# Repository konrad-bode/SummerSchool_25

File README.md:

# HeiChips 2025 SummerSchool – FPGA Carrier Board

This repository contains the KiCad hardware design for the **HeiChips 2025 SummerSchool FPGA Carrier Board**, designed to interface with the custom tapeout FPGA chip from the [HeiChips 2025 Tapeout Repository](https://github.com/HeiChips/heichips25-tapeout).

---

## 🏗 System Overview

The carrier board interfaces with a custom HeiChips FPGA breakout module via a 70-pin high-density mezzanine connector. An onboard RP2350A microcontroller handles FPGA configuration.

---

## ⚡ Key Hardware Features

### Onboard Controller & Configuration
* **Microcontroller:** RP2350A MCU managing FPGA boot configuration (`FPGA_CONFIG_SLOT[0..3]`), reset, clocks, and SPI interface.
* **Flash Memory:** Dual W25Q32JVSS QSPI Flash ICs (one for RP2350, one for FPGA image storage).
* **Control Switches:** 74LVC1G66 analog switch for SPI bus arbitration.

### Power Management
* **Input Power:** 5V DC input via USB-C
* **System 3.3V:** TLV1117-33 LDO supplying 3.3V rail from 5V input for FPGA IO and Microcontroller
* **FPGA Core Supply (`VCORE`/`AVCORE`):** AP7361C adjustable LDO 

### Connectors & Peripherals
* **Module Interconnect:** 70-pin Amphenol BergStak Mezzanine Receptacle (`10164227-0701A1RLF`).
* **Expansion:** 4x PMOD headers (`J20`–`J23`) routing FPGA `GPIO0`–`GPIO31`.
* **Video Output:** HDMI interface (`J18`) driven by DS90LV027A LVDS differential line drivers.
* **USB Ports:** Dual USB-C connectors (`J17` for RP2350 debug/programming, `J19` directly connected to FPGA USB with ESD protection).
* **Analog & RF:** Coaxial SMA/MCX connectors for IceLab analog pins, internal analog signals, and Pudding I/O lines.
* **Ethernet:** 3-pin Ethernet header (`J8`).

---

## TODO
- [ ] HDMI differential pair length matching and impedance tuning.
- [ ] Project selection per jumper
- [ ] Connect GPIOs from FPGA to Microcontroller UART? 
- [ ] Check SMA distance

---

## 👤 Author
* **Konrad Bode**

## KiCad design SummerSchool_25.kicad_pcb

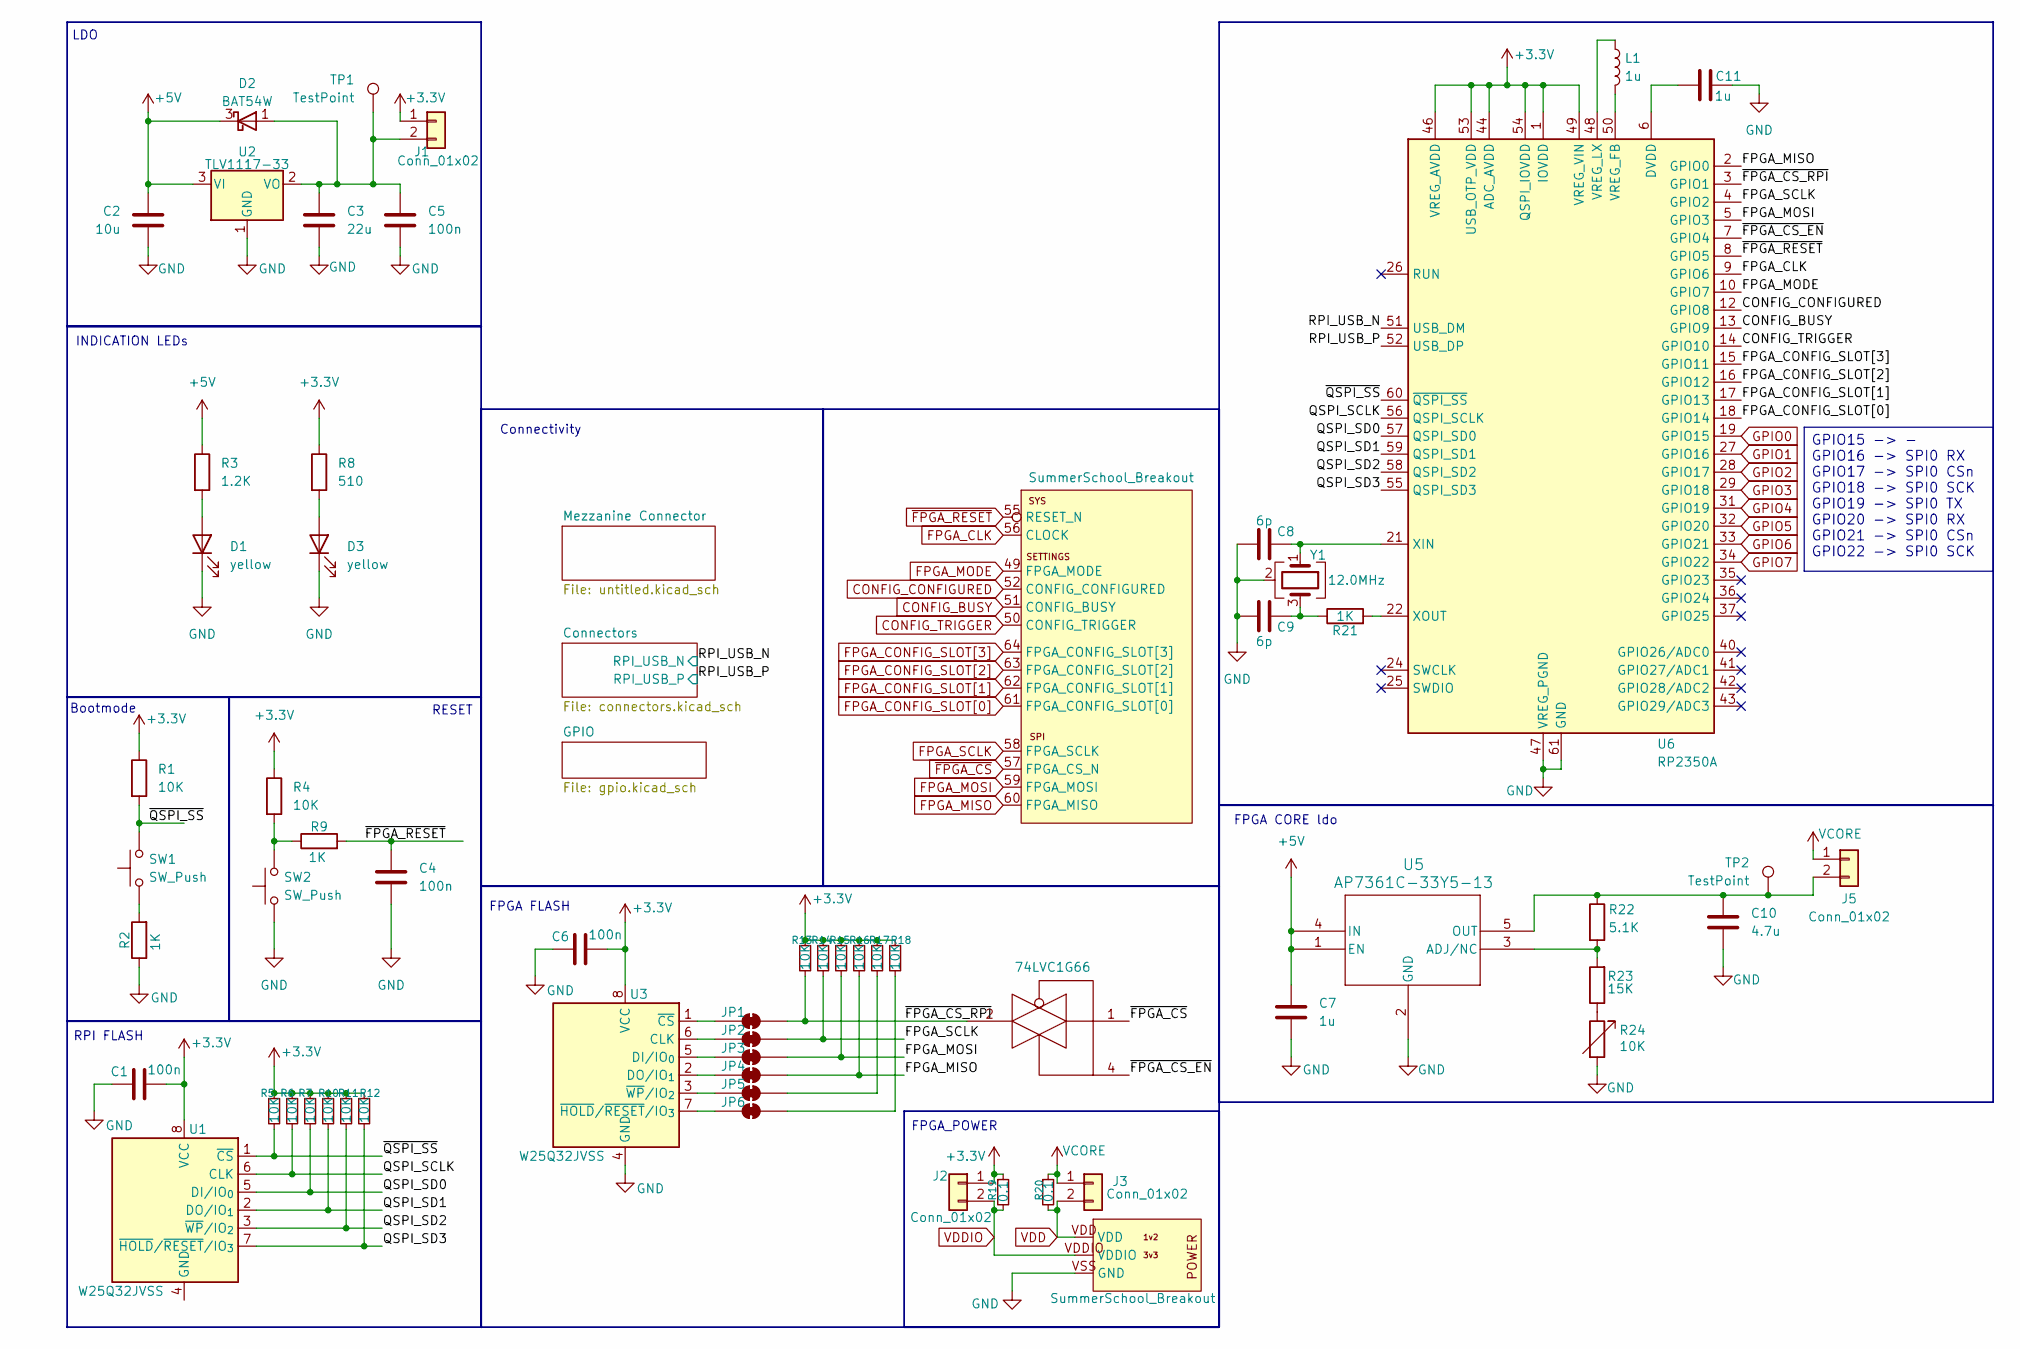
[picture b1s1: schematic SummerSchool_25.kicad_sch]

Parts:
C1, C4, C5, C6: 100n; C_0603_1608Metric
C2: 10u; C_0603_1608Metric
C3: 22u; C_0603_1608Metric
C7, C11: 1u; C_0603_1608Metric
C8, C9: 6p; C_0603_1608Metric
C10: 4.7u; C_0603_1608Metric
D1, D3: yellow; LED_0603_1608Metric
D2: BAT54W; SOT-323_SC-70
J1, J2, J3, J5: Conn_01x02; PinHeader_1x02_P2.54mm_Vertical
J4: SummerSchool_Breakout; SummerSchool_WireBond
JP1, JP2, JP3, JP4, JP5, JP6: SolderJumper_2_Bridged; SolderJumper-2_P1.3mm_Bridged2Bar_RoundedPad1.0x1.5mm
L1: 1u; L_1008_2520Metric
R1, R4, R5, R6, R7, R10, R11, R12, R13, R14, R15, R16, R17, R18: 10K; R_0402_1005Metric
R2, R9, R21: 1K; R_0402_1005Metric
R3: 1.2K; R_0402_1005Metric
R8: 510; R_0402_1005Metric
R19, R20: 0.1; R_0805_2012Metric
R22: 5.1K; R_0402_1005Metric
R23: 15K; R_0402_1005Metric
R24: 10K; R_LDR_5.2x5.2mm_P3.5mm_Horizontal
SW1, SW2: SW_Push; SW_SPST_EVQP2_MiddlePushTravel_H2.5mm
TP1, TP2: TestPoint; TestPoint_Pad_1.5x1.5mm
U1, U3: W25Q32JVSS; SOIC-8_5.3x5.3mm_P1.27mm
U2: TLV1117-33; TO-252-2
U4: 74LVC1G66; SOT-553
U5: AP7361C-33Y5-13; SOT89-5_DIO
U6: RP2350A; QFN-60-1EP_7x7mm_P0.4mm_EP3.4x3.4mm
Y1: 12.0MHz; Crystal_SMD_3225-4Pin_3.2x2.5mm

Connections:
+3.3V: C1.2, C6.2, J1.1, J2.1, R1.1, R4.1, R5.1, R6.1, R7.1, R8.1, R10.1, R11.1, R12.1, R13.1, R14.1, R15.1, R16.1, R17.1, R18.1, R19.1, U1.8 (VCC), U3.8 (VCC), U6.1 (IOVDD), U6.11 (IOVDD), U6.20 (IOVDD), U6.30 (IOVDD), U6.38 (IOVDD), U6.44 (ADC_AVDD), U6.45 (IOVDD), U6.46 (VREG_AVDD), U6.49 (VREG_VIN), U6.53 (USB_OTP_VDD), U6.54 (QSPI_IOVDD); also elsewhere on the board
+5V: C2.1, C7.1, D2.3 (K), R3.1, U2.3 (VI), U5.1 (EN), U5.4 (IN); also elsewhere on the board
/QSPI_SCLK: R6.2, U1.6 (CLK), U6.56 (QSPI_SCLK)
/QSPI_SD0: R7.2, U1.5 (DI/IO_{0}), U6.57 (QSPI_SD0)
/QSPI_SD1: R10.2, U1.2 (DO/IO_{1}), U6.59 (QSPI_SD1)
/QSPI_SD2: R11.2, U1.3 (~WP/IO_{2}), U6.58 (QSPI_SD2)
/QSPI_SD3: R12.2, U1.7 (~HOLD/~RESET/IO_{3}), U6.55 (QSPI_SD3)
/RPI_USB_N: U6.51 (USB_DM); also elsewhere on the board
/RPI_USB_P: U6.52 (USB_DP); also elsewhere on the board
/~FPGA_CS_EN: U4.4, U6.7 (GPIO4)
/~FPGA_CS_RPI: JP1.2 (B), R13.2, U4.2, U6.3 (GPIO1)
/~QSPI_SS: R1.2, R5.2, SW1.2, U1.1 (~CS), U6.60 (~QSPI_SS)
CONFIG_BUSY: U6.13 (GPIO9); also elsewhere on the board
CONFIG_CONFIGURED: U6.12 (GPIO8); also elsewhere on the board
CONFIG_TRIGGER: U6.14 (GPIO10); also elsewhere on the board
FPGA_CLK: U6.9 (GPIO6); also elsewhere on the board
FPGA_CONFIG_SLOT[0]: U6.18 (GPIO14); also elsewhere on the board
FPGA_CONFIG_SLOT[1]: U6.17 (GPIO13); also elsewhere on the board
FPGA_CONFIG_SLOT[2]: U6.16 (GPIO12); also elsewhere on the board
FPGA_CONFIG_SLOT[3]: U6.15 (GPIO11); also elsewhere on the board
FPGA_MISO: JP4.2 (B), R16.2, U6.2 (GPIO0); also elsewhere on the board
FPGA_MODE: U6.10 (GPIO7); also elsewhere on the board
FPGA_MOSI: JP3.2 (B), R15.2, U6.5 (GPIO3); also elsewhere on the board
FPGA_SCLK: JP2.2 (B), R14.2, U6.4 (GPIO2); also elsewhere on the board
GND: C1.1, C2.2, C3.2, C4.2, C5.2, C6.1, C7.2, C8.1, C9.1, C10.2, C11.2, D1.1 (K), D3.1 (K), J4.VSS (GND), R2.1, R24.2, SW2.1, U2.1 (GND), U3.4 (GND), U5.2 (GND), U6.47 (VREG_PGND), U6.61 (GND), Y1.2 (G), Y1.4 (G); also elsewhere on the board
GPIO0: U6.19 (GPIO15); also elsewhere on the board
GPIO1: U6.27 (GPIO16); also elsewhere on the board
GPIO2: U6.28 (GPIO17); also elsewhere on the board
GPIO3: U6.29 (GPIO18); also elsewhere on the board
GPIO4: U6.31 (GPIO19); also elsewhere on the board
GPIO5: U6.32 (GPIO20); also elsewhere on the board
GPIO6: U6.33 (GPIO21); also elsewhere on the board
GPIO7: U6.34 (GPIO22); also elsewhere on the board
unnamed: C9.2, R21.1, Y1.3
unnamed: C11.1, U6.6 (DVDD), U6.23 (DVDD), U6.39 (DVDD)
unnamed: D1.2 (A), R3.2
unnamed: C3.1, C5.1, D2.1 (A), J1.2, TP1.1 (1_1), U2.2 (VO)
unnamed: D3.2 (A), R8.2
unnamed: C10.1, J5.2, R22.1, TP2.1 (1_1), U5.5 (OUT)
unnamed: JP1.1 (A), U3.1 (~CS)
unnamed: JP2.1 (A), U3.6 (CLK)
unnamed: JP3.1 (A), U3.5 (DI/IO_{0})
unnamed: JP4.1 (A), U3.2 (DO/IO_{1})
unnamed: JP5.1 (A), U3.3 (~WP/IO_{2})
unnamed: JP5.2 (B), R17.2
unnamed: JP6.1 (A), U3.7 (~HOLD/~RESET/IO_{3})
unnamed: JP6.2 (B), R18.2
unnamed: R2.2, SW1.1
unnamed: R4.2, R9.1, SW2.2
unnamed: R23.1, R24.1
unnamed: R22.2, R23.2, U5.3 (ADJ/NC)
unnamed: L1.2, U6.50 (VREG_FB)
unnamed: L1.1, U6.48 (VREG_LX)
unnamed: C8.2, U6.21 (XIN), Y1.1
unnamed: R21.2, U6.22 (XOUT)
VCORE: J3.1, J5.1, R20.1
VDD: J3.2, J4.VDD, R20.2; also elsewhere on the board
VDDIO: J2.2, J4.VDDIO, R19.2; also elsewhere on the board
~FPGA_CS: U4.1; also elsewhere on the board
~FPGA_RESET: C4.1, R9.2, U6.8 (GPIO5); also elsewhere on the board

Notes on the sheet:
Connectivity
RESET
RPI FLASH
INDICATION LEDs
FPGA_POWER
FPGA CORE ldo
FPGA FLASH
Bootmode
LDO
GPIO15 -> - GPIO16 -> SPI0 RX GPIO17 -> SPI0 CSn GPIO18 -> SPI0 SCK GPIO19 -> SPI0 TX GPIO20 -> SPI0 RX GPIO21 -> SPI0 CSn GPIO22 -> SPI0 SCK

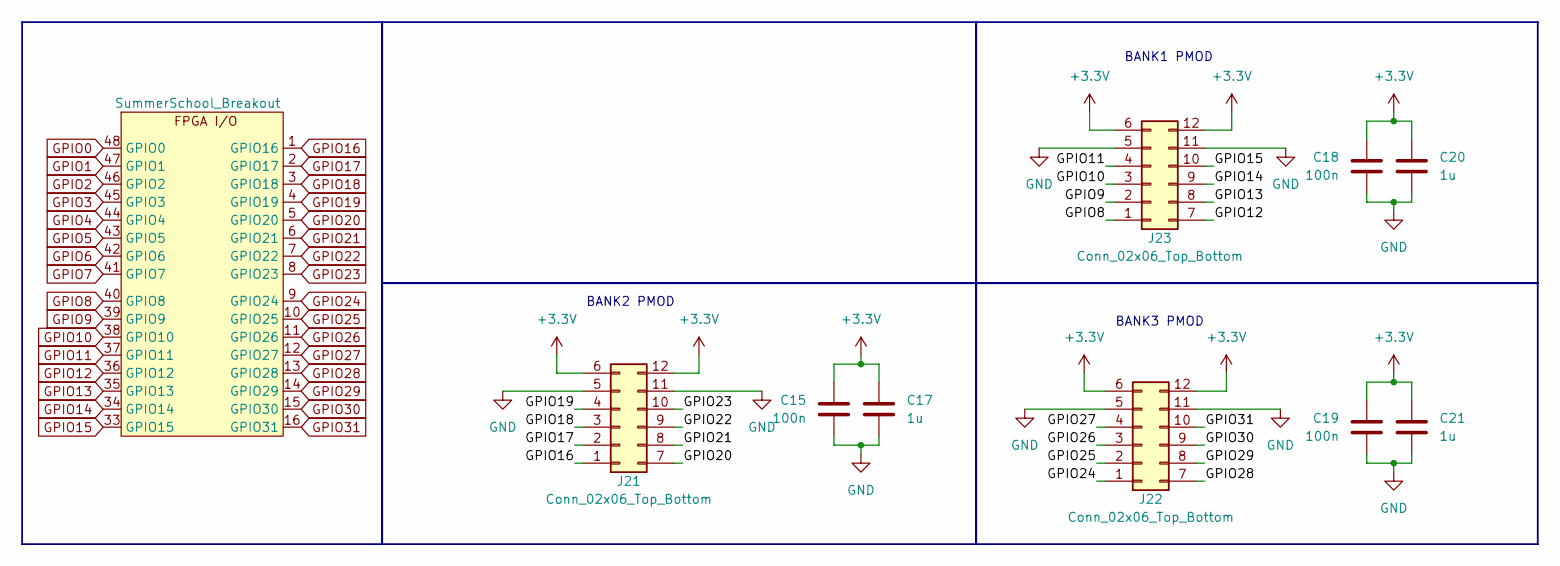
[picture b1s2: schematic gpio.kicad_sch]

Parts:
C15, C18, C19: 100n; C_0603_1608Metric
C17, C20, C21: 1u; C_0603_1608Metric
J4: SummerSchool_Breakout; SummerSchool_WireBond
J21, J22, J23: Conn_02x06_Top_Bottom; PinSocket_2x06_P2.54mm_Horizontal

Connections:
+3.3V: C15.1, C17.1, C18.1, C19.1, C20.1, C21.1, J21.6, J21.12, J22.6, J22.12, J23.6, J23.12; also elsewhere on the board
GND: C15.2, C17.2, C18.2, C19.2, C20.2, C21.2, J21.5, J21.11, J22.5, J22.11, J23.5, J23.11; also elsewhere on the board
GPIO8: J23.1; also elsewhere on the board
GPIO9: J23.2; also elsewhere on the board
GPIO10: J23.3; also elsewhere on the board
GPIO11: J23.4; also elsewhere on the board
GPIO12: J23.7; also elsewhere on the board
GPIO13: J23.8; also elsewhere on the board
GPIO14: J23.9; also elsewhere on the board
GPIO15: J23.10; also elsewhere on the board
GPIO16: J21.1; also elsewhere on the board
GPIO17: J21.2; also elsewhere on the board
GPIO18: J21.3; also elsewhere on the board
GPIO19: J21.4; also elsewhere on the board
GPIO20: J21.7; also elsewhere on the board
GPIO21: J21.8; also elsewhere on the board
GPIO22: J21.9; also elsewhere on the board
GPIO23: J21.10; also elsewhere on the board
GPIO24: J22.1; also elsewhere on the board
GPIO25: J22.2; also elsewhere on the board
GPIO26: J22.3; also elsewhere on the board
GPIO27: J22.4; also elsewhere on the board
GPIO28: J22.7; also elsewhere on the board
GPIO29: J22.8; also elsewhere on the board
GPIO30: J22.9; also elsewhere on the board
GPIO31: J22.10; also elsewhere on the board

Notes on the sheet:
BANK1 PMOD
BANK3 PMOD
BANK2 PMOD

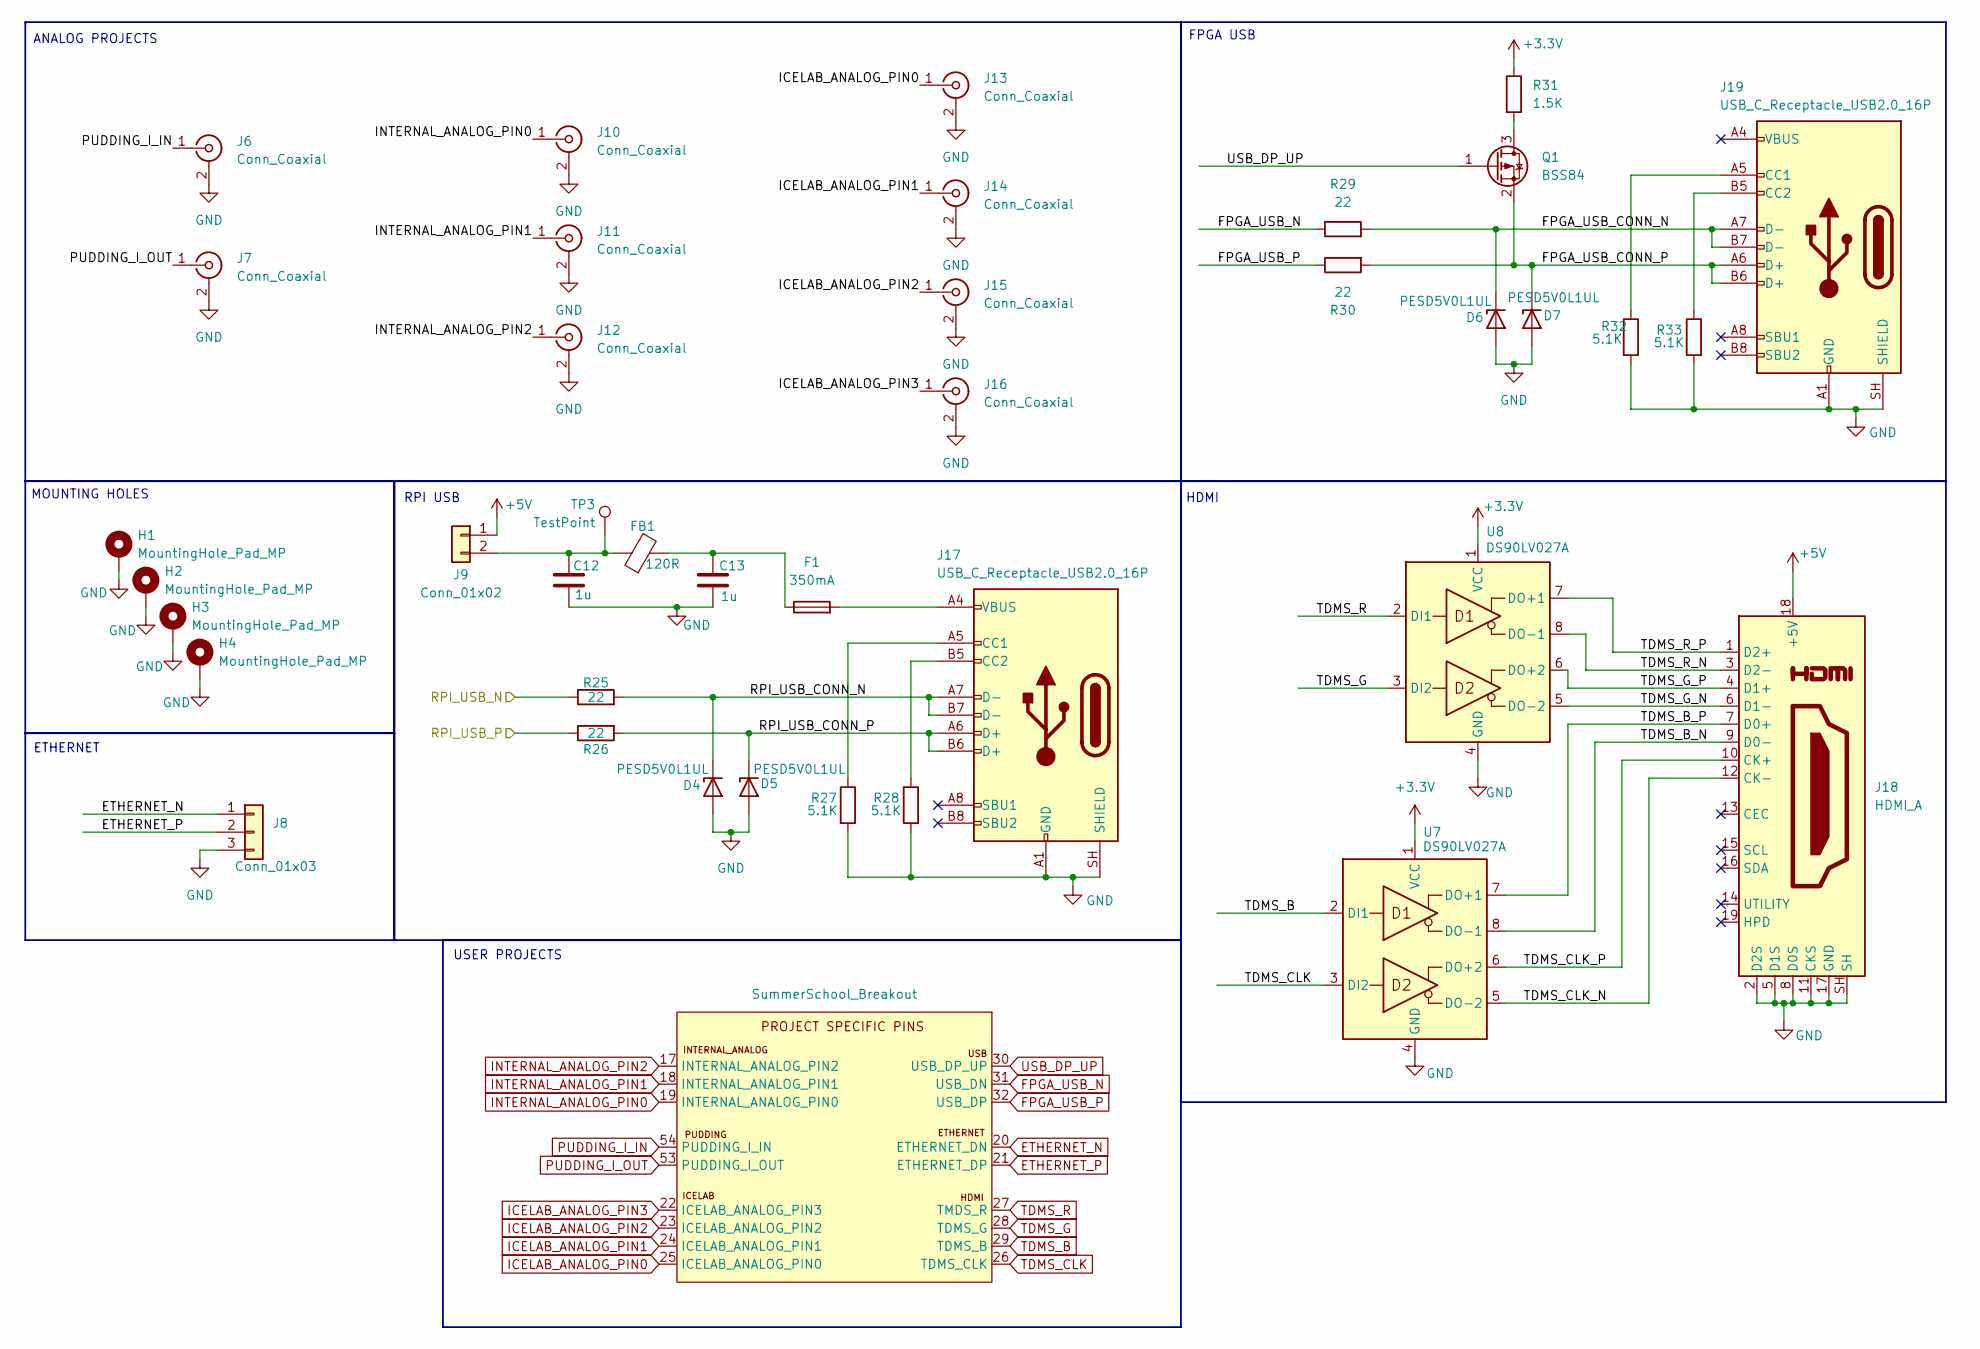
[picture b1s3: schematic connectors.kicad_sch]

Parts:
C12, C13: 1u; C_0603_1608Metric
D4, D5, D6, D7: PESD5V0L1UL; D_SOD-882
F1: 350mA; Fuse_0603_1608Metric
FB1: 120R; L_Eaton_MCL2012V1
H1, H2, H3, H4: MountingHole_Pad_MP; MountingHole_2.5mm_Pad_TopBottom
J4: SummerSchool_Breakout; SummerSchool_WireBond
J6, J7, J10, J11, J12, J13, J14, J15, J16: Conn_Coaxial; SMA_Amphenol_132134_Vertical
J8: Conn_01x03; FanPinHeader_1x03_P2.54mm_Vertical
J9: Conn_01x02; PinHeader_1x02_P2.54mm_Vertical
J17, J19: USB_C_Receptacle_USB2.0_16P; USB_C_Receptacle_XKB_U262-16XN-4BVC11
J18: HDMI_A; HDMI_A_Molex_208658-1001_Horizontal
Q1: BSS84; SOT-23
R25, R26, R29, R30: 22; R_0402_1005Metric
R27, R28, R32, R33: 5.1K; R_0402_1005Metric
R31: 1.5K; R_0402_1005Metric
TP3: TestPoint; TestPoint_Pad_1.5x1.5mm
U7, U8: DS90LV027A; SOIC-8_3.9x4.9mm_P1.27mm

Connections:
+3.3V: R31.1, U7.1 (VCC), U8.1 (VCC); also elsewhere on the board
+5V: J9.1, J18.18 (+5V); also elsewhere on the board
/Connectors/FPGA_USB_CONN_N: D6.1 (K), J19.A7 (D-), J19.B7 (D-), R29.2
/Connectors/FPGA_USB_CONN_P: D7.1 (K), J19.A6 (D+), J19.B6 (D+), Q1.2 (S), R30.2
/Connectors/RPI_USB_CONN_N: D4.1 (K), J17.A7 (D-), J17.B7 (D-), R25.2
/Connectors/RPI_USB_CONN_P: D5.1 (K), J17.A6 (D+), J17.B6 (D+), R26.2
/Connectors/TDMS_B_N: J18.9 (D0-), U7.8 (DO-1)
/Connectors/TDMS_B_P: J18.7 (D0+), U7.7 (DO+1)
/Connectors/TDMS_CLK_N: J18.12 (CK-), U7.5 (DO-2)
/Connectors/TDMS_CLK_P: J18.10 (CK+), U7.6 (DO+2)
/Connectors/TDMS_G_N: J18.6 (D1-), U8.5 (DO-2)
/Connectors/TDMS_G_P: J18.4 (D1+), U8.6 (DO+2)
/Connectors/TDMS_R_N: J18.3 (D2-), U8.8 (DO-1)
/Connectors/TDMS_R_P: J18.1 (D2+), U8.7 (DO+1)
/RPI_USB_N: R25.1; also elsewhere on the board
/RPI_USB_P: R26.1; also elsewhere on the board
ETHERNET_N: J8.1; also elsewhere on the board
ETHERNET_P: J8.2; also elsewhere on the board
FPGA_USB_N: R29.1; also elsewhere on the board
FPGA_USB_P: R30.1; also elsewhere on the board
GND: C12.2, C13.2, D4.2 (A), D5.2 (A), D6.2 (A), D7.2 (A), H1.1 (MP_1), H2.1 (MP_1), H3.1 (MP_1), H4.1 (MP_1), J6.2 (Ext), J7.2 (Ext), J8.3, J10.2 (Ext), J11.2 (Ext), J12.2 (Ext), J13.2 (Ext), J14.2 (Ext), J15.2 (Ext), J16.2 (Ext), J17.A1 (GND), J17.A12 (GND), J17.B1 (GND), J17.B12 (GND), J17.SH (SHIELD), J18.2 (D2S), J18.5 (D1S), J18.8 (D0S), J18.11 (CKS), J18.17 (GND), J18.SH, J19.A1 (GND), J19.A12 (GND), J19.B1 (GND), J19.B12 (GND), J19.SH (SHIELD), R27.2, R28.2, R32.2, R33.2, U7.4 (GND), U8.4 (GND); also elsewhere on the board
ICELAB_ANALOG_PIN0: J13.1 (In); also elsewhere on the board
ICELAB_ANALOG_PIN1: J14.1 (In); also elsewhere on the board
ICELAB_ANALOG_PIN2: J15.1 (In); also elsewhere on the board
ICELAB_ANALOG_PIN3: J16.1 (In); also elsewhere on the board
INTERNAL_ANALOG_PIN0: J10.1 (In); also elsewhere on the board
INTERNAL_ANALOG_PIN1: J11.1 (In); also elsewhere on the board
INTERNAL_ANALOG_PIN2: J12.1 (In); also elsewhere on the board
unnamed: C13.1, F1.1, FB1.2
unnamed: F1.2, J17.A4 (VBUS), J17.A9 (VBUS), J17.B4 (VBUS), J17.B9 (VBUS)
unnamed: C12.1, FB1.1, J9.2, TP3.1 (1_1)
unnamed: J17.A5 (CC1), R27.1
unnamed: J17.B5 (CC2), R28.1
unnamed: J19.A5 (CC1), R32.1
unnamed: J19.B5 (CC2), R33.1
unnamed: Q1.3 (D), R31.2
PUDDING_I_IN: J6.1 (In); also elsewhere on the board
PUDDING_I_OUT: J7.1 (In); also elsewhere on the board
TDMS_B: U7.2 (DI1); also elsewhere on the board
TDMS_CLK: U7.3 (DI2); also elsewhere on the board
TDMS_G: U8.3 (DI2); also elsewhere on the board
TDMS_R: U8.2 (DI1); also elsewhere on the board
USB_DP_UP: Q1.1 (G); also elsewhere on the board

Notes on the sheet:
ETHERNET
RPI USB
FPGA USB
HDMI
ANALOG PROJECTS
USER PROJECTS
MOUNTING HOLES

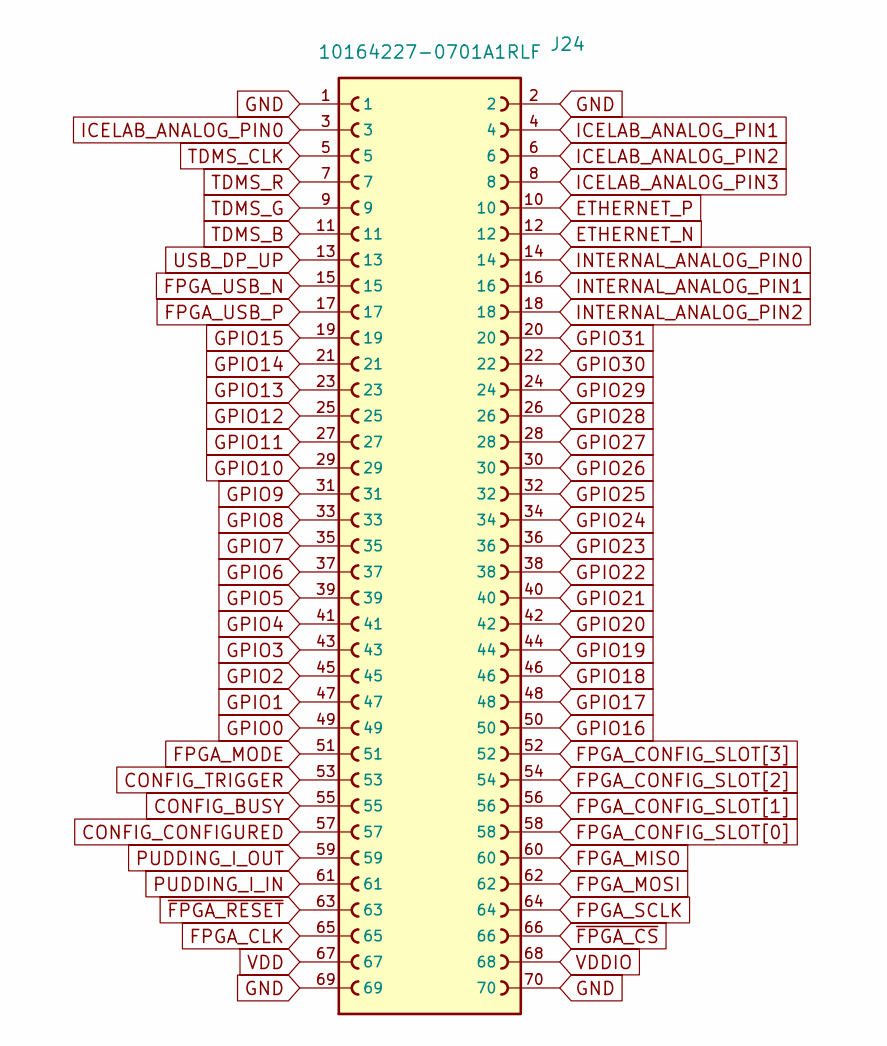
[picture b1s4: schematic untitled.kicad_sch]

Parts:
J24: 10164227-0701A1RLF; AMPHENOL_10164227-0701A1RLF; PARTREV C

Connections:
CONFIG_BUSY: J24.55; also elsewhere on the board
CONFIG_CONFIGURED: J24.57; also elsewhere on the board
CONFIG_TRIGGER: J24.53; also elsewhere on the board
ETHERNET_N: J24.12; also elsewhere on the board
ETHERNET_P: J24.10; also elsewhere on the board
FPGA_CLK: J24.65; also elsewhere on the board
FPGA_CONFIG_SLOT[0]: J24.58; also elsewhere on the board
FPGA_CONFIG_SLOT[1]: J24.56; also elsewhere on the board
FPGA_CONFIG_SLOT[2]: J24.54; also elsewhere on the board
FPGA_CONFIG_SLOT[3]: J24.52; also elsewhere on the board
FPGA_MISO: J24.60; also elsewhere on the board
FPGA_MODE: J24.51; also elsewhere on the board
FPGA_MOSI: J24.62; also elsewhere on the board
FPGA_SCLK: J24.64; also elsewhere on the board
FPGA_USB_N: J24.15; also elsewhere on the board
FPGA_USB_P: J24.17; also elsewhere on the board
GND: J24.1, J24.2, J24.69, J24.70; also elsewhere on the board
GPIO0: J24.49; also elsewhere on the board
GPIO1: J24.47; also elsewhere on the board
GPIO2: J24.45; also elsewhere on the board
GPIO3: J24.43; also elsewhere on the board
GPIO4: J24.41; also elsewhere on the board
GPIO5: J24.39; also elsewhere on the board
GPIO6: J24.37; also elsewhere on the board
GPIO7: J24.35; also elsewhere on the board
GPIO8: J24.33; also elsewhere on the board
GPIO9: J24.31; also elsewhere on the board
GPIO10: J24.29; also elsewhere on the board
GPIO11: J24.27; also elsewhere on the board
GPIO12: J24.25; also elsewhere on the board
GPIO13: J24.23; also elsewhere on the board
GPIO14: J24.21; also elsewhere on the board
GPIO15: J24.19; also elsewhere on the board
GPIO16: J24.50; also elsewhere on the board
GPIO17: J24.48; also elsewhere on the board
GPIO18: J24.46; also elsewhere on the board
GPIO19: J24.44; also elsewhere on the board
GPIO20: J24.42; also elsewhere on the board
GPIO21: J24.40; also elsewhere on the board
GPIO22: J24.38; also elsewhere on the board
GPIO23: J24.36; also elsewhere on the board
GPIO24: J24.34; also elsewhere on the board
GPIO25: J24.32; also elsewhere on the board
GPIO26: J24.30; also elsewhere on the board
GPIO27: J24.28; also elsewhere on the board
GPIO28: J24.26; also elsewhere on the board
GPIO29: J24.24; also elsewhere on the board
GPIO30: J24.22; also elsewhere on the board
GPIO31: J24.20; also elsewhere on the board
ICELAB_ANALOG_PIN0: J24.3; also elsewhere on the board
ICELAB_ANALOG_PIN1: J24.4; also elsewhere on the board
ICELAB_ANALOG_PIN2: J24.6; also elsewhere on the board
ICELAB_ANALOG_PIN3: J24.8; also elsewhere on the board
INTERNAL_ANALOG_PIN0: J24.14; also elsewhere on the board
INTERNAL_ANALOG_PIN1: J24.16; also elsewhere on the board
INTERNAL_ANALOG_PIN2: J24.18; also elsewhere on the board
PUDDING_I_IN: J24.61; also elsewhere on the board
PUDDING_I_OUT: J24.59; also elsewhere on the board
TDMS_B: J24.11; also elsewhere on the board
TDMS_CLK: J24.5; also elsewhere on the board
TDMS_G: J24.9; also elsewhere on the board
TDMS_R: J24.7; also elsewhere on the board
USB_DP_UP: J24.13; also elsewhere on the board
VDD: J24.67; also elsewhere on the board
VDDIO: J24.68; also elsewhere on the board
~FPGA_CS: J24.66; also elsewhere on the board
~FPGA_RESET: J24.63; also elsewhere on the board

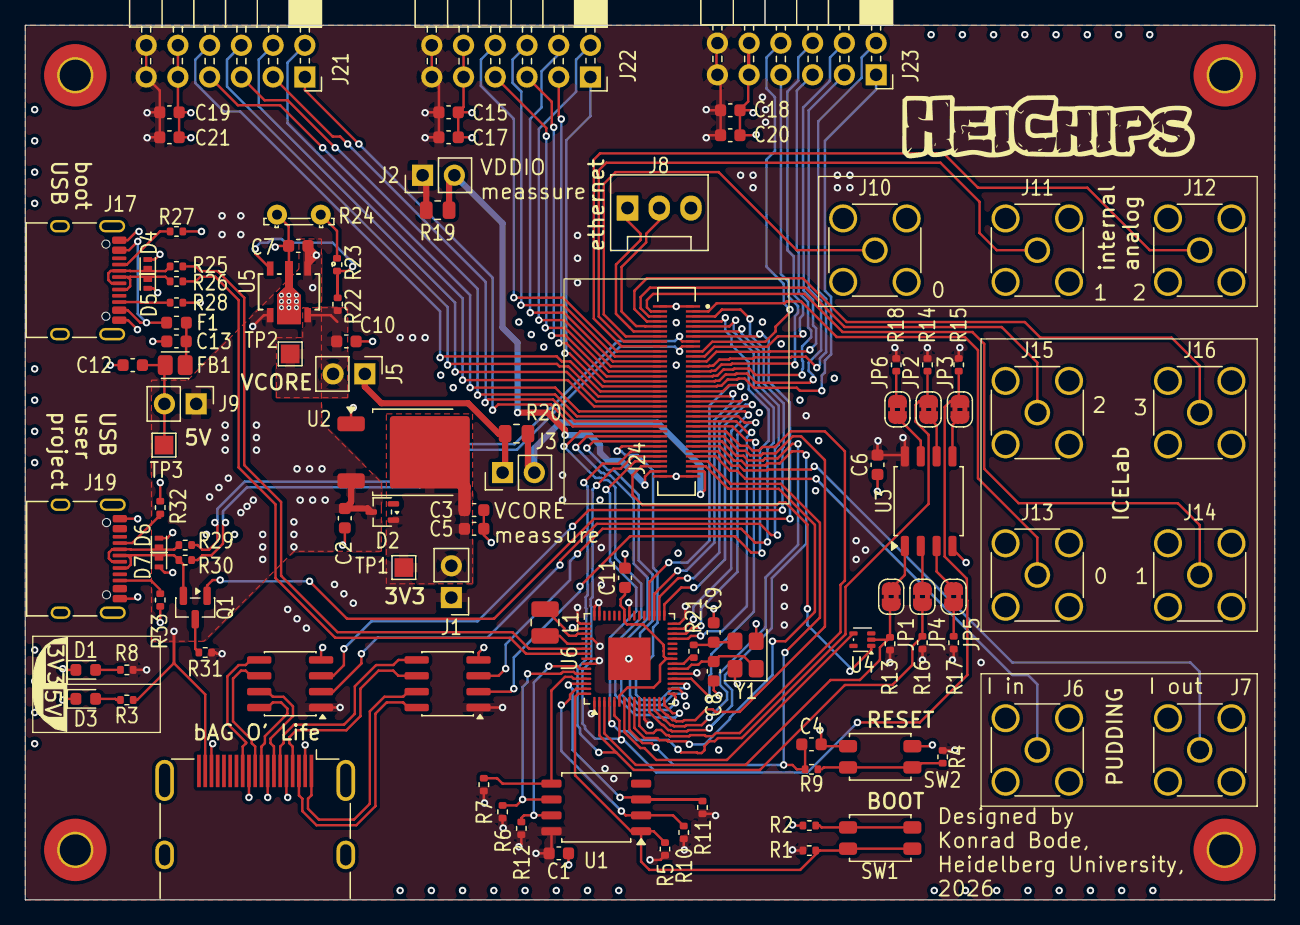
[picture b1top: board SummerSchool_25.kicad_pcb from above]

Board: 4 copper layers, 100.0 x 70.0 mm, 109 parts (0 on the bottom side), 122 nets.

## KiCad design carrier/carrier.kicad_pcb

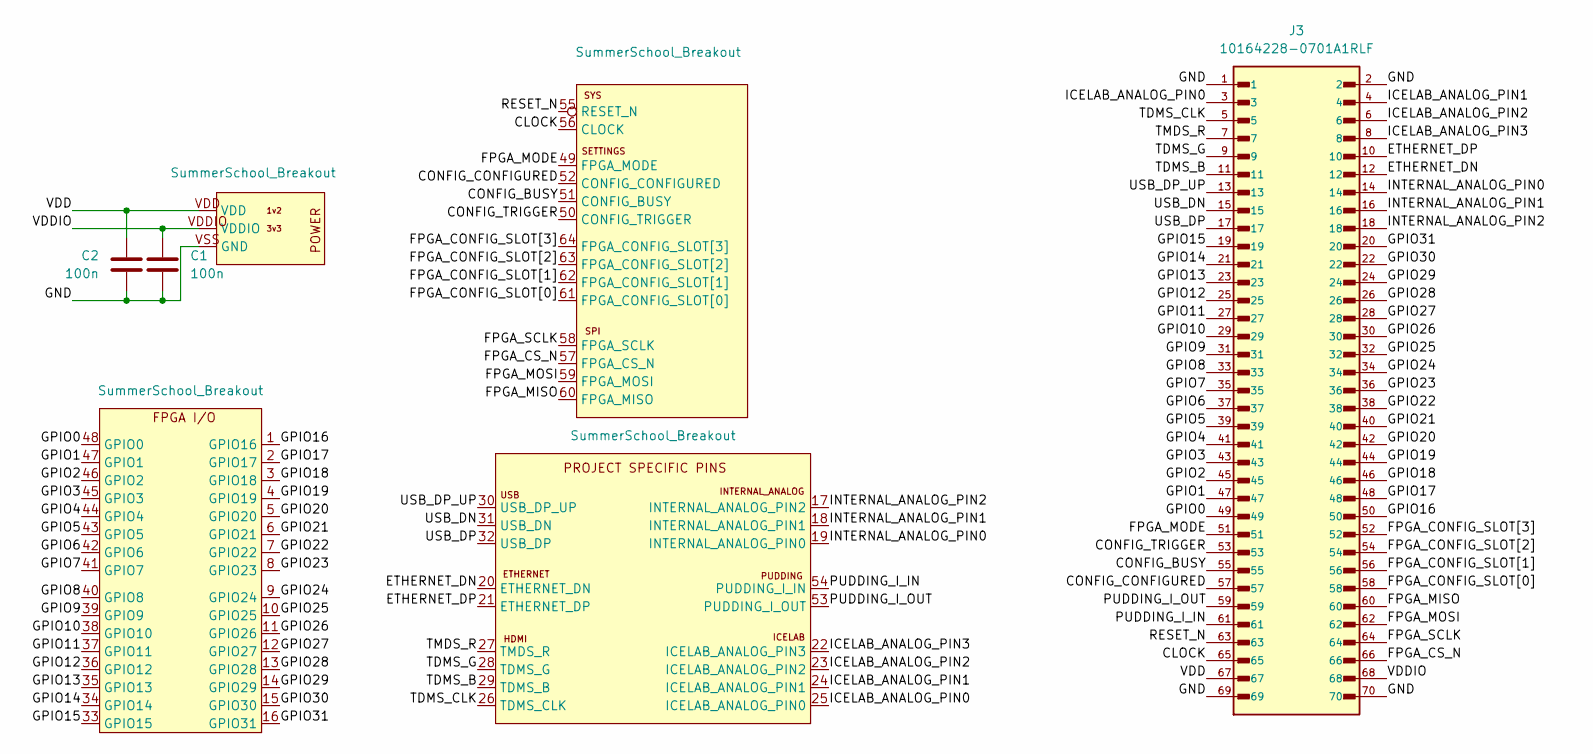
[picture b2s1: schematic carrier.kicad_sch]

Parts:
C1, C2: 100n; C_0603_1608Metric
J1: SummerSchool_Breakout; SummerSchool_WireBond
J3: 10164228-0701A1RLF; AMPHENOL_10164228-0701A1RLF; PARTREV C

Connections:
/CLOCK: J1.56 (CLOCK), J3.65
/CONFIG_BUSY: J1.51 (CONFIG_BUSY), J3.55
/CONFIG_CONFIGURED: J1.52 (CONFIG_CONFIGURED), J3.57
/CONFIG_TRIGGER: J1.50 (CONFIG_TRIGGER), J3.53
/ETHERNET_DN: J1.20 (ETHERNET_DN), J3.12
/ETHERNET_DP: J1.21 (ETHERNET_DP), J3.10
/FPGA_CONFIG_SLOT[0]: J1.61 (FPGA_CONFIG_SLOT[0]), J3.58
/FPGA_CONFIG_SLOT[1]: J1.62 (FPGA_CONFIG_SLOT[1]), J3.56
/FPGA_CONFIG_SLOT[2]: J1.63 (FPGA_CONFIG_SLOT[2]), J3.54
/FPGA_CONFIG_SLOT[3]: J1.64 (FPGA_CONFIG_SLOT[3]), J3.52
/FPGA_CS_N: J1.57 (FPGA_CS_N), J3.66
/FPGA_MISO: J1.60 (FPGA_MISO), J3.60
/FPGA_MODE: J1.49 (FPGA_MODE), J3.51
/FPGA_MOSI: J1.59 (FPGA_MOSI), J3.62
/FPGA_SCLK: J1.58 (FPGA_SCLK), J3.64
/GND: C1.2, C2.1, J1.VSS (GND), J3.1, J3.2, J3.69, J3.70
/GPIO0: J1.48 (GPIO0), J3.49
/GPIO1: J1.47 (GPIO1), J3.47
/GPIO2: J1.46 (GPIO2), J3.45
/GPIO3: J1.45 (GPIO3), J3.43
/GPIO4: J1.44 (GPIO4), J3.41
/GPIO5: J1.43 (GPIO5), J3.39
/GPIO6: J1.42 (GPIO6), J3.37
/GPIO7: J1.41 (GPIO7), J3.35
/GPIO8: J1.40 (GPIO8), J3.33
/GPIO9: J1.39 (GPIO9), J3.31
/GPIO10: J1.38 (GPIO10), J3.29
/GPIO11: J1.37 (GPIO11), J3.27
/GPIO12: J1.36 (GPIO12), J3.25
/GPIO13: J1.35 (GPIO13), J3.23
/GPIO14: J1.34 (GPIO14), J3.21
/GPIO15: J1.33 (GPIO15), J3.19
/GPIO16: J1.1 (GPIO16), J3.50
/GPIO17: J1.2 (GPIO17), J3.48
/GPIO18: J1.3 (GPIO18), J3.46
/GPIO19: J1.4 (GPIO19), J3.44
/GPIO20: J1.5 (GPIO20), J3.42
/GPIO21: J1.6 (GPIO21), J3.40
/GPIO22: J1.7 (GPIO22), J3.38
/GPIO23: J1.8 (GPIO23), J3.36
/GPIO24: J1.9 (GPIO24), J3.34
/GPIO25: J1.10 (GPIO25), J3.32
/GPIO26: J1.11 (GPIO26), J3.30
/GPIO27: J1.12 (GPIO27), J3.28
/GPIO28: J1.13 (GPIO28), J3.26
/GPIO29: J1.14 (GPIO29), J3.24
/GPIO30: J1.15 (GPIO30), J3.22
/GPIO31: J1.16 (GPIO31), J3.20
/ICELAB_ANALOG_PIN0: J1.25 (ICELAB_ANALOG_PIN0), J3.3
/ICELAB_ANALOG_PIN1: J1.24 (ICELAB_ANALOG_PIN1), J3.4
/ICELAB_ANALOG_PIN2: J1.23 (ICELAB_ANALOG_PIN2), J3.6
/ICELAB_ANALOG_PIN3: J1.22 (ICELAB_ANALOG_PIN3), J3.8
/INTERNAL_ANALOG_PIN0: J1.19 (INTERNAL_ANALOG_PIN0), J3.14
/INTERNAL_ANALOG_PIN1: J1.18 (INTERNAL_ANALOG_PIN1), J3.16
/INTERNAL_ANALOG_PIN2: J1.17 (INTERNAL_ANALOG_PIN2), J3.18
/PUDDING_I_IN: J1.54 (PUDDING_I_IN), J3.61
/PUDDING_I_OUT: J1.53 (PUDDING_I_OUT), J3.59
/RESET_N: J1.55 (RESET_N), J3.63
/TDMS_B: J1.29 (TDMS_B), J3.11
/TDMS_CLK: J1.26 (TDMS_CLK), J3.5
/TDMS_G: J1.28 (TDMS_G), J3.9
/TMDS_R: J1.27 (TMDS_R), J3.7
/USB_DN: J1.31 (USB_DN), J3.15
/USB_DP: J1.32 (USB_DP), J3.17
/USB_DP_UP: J1.30 (USB_DP_UP), J3.13
/VDD: C2.2, J1.VDD, J3.67
/VDDIO: C1.1, J1.VDDIO, J3.68

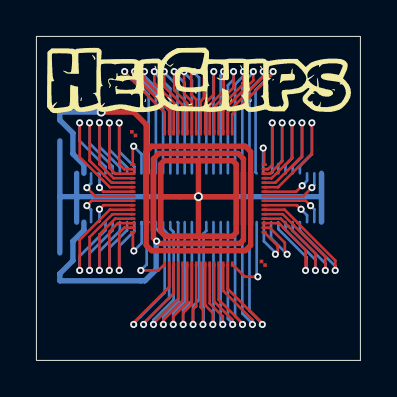
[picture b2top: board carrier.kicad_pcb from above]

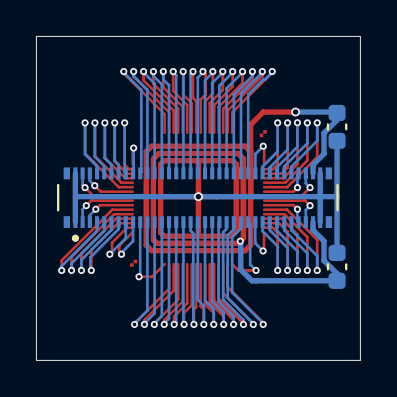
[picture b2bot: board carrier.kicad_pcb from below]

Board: 2 copper layers, 18.0 x 18.0 mm, 4 parts (3 on the bottom side), 67 nets.
